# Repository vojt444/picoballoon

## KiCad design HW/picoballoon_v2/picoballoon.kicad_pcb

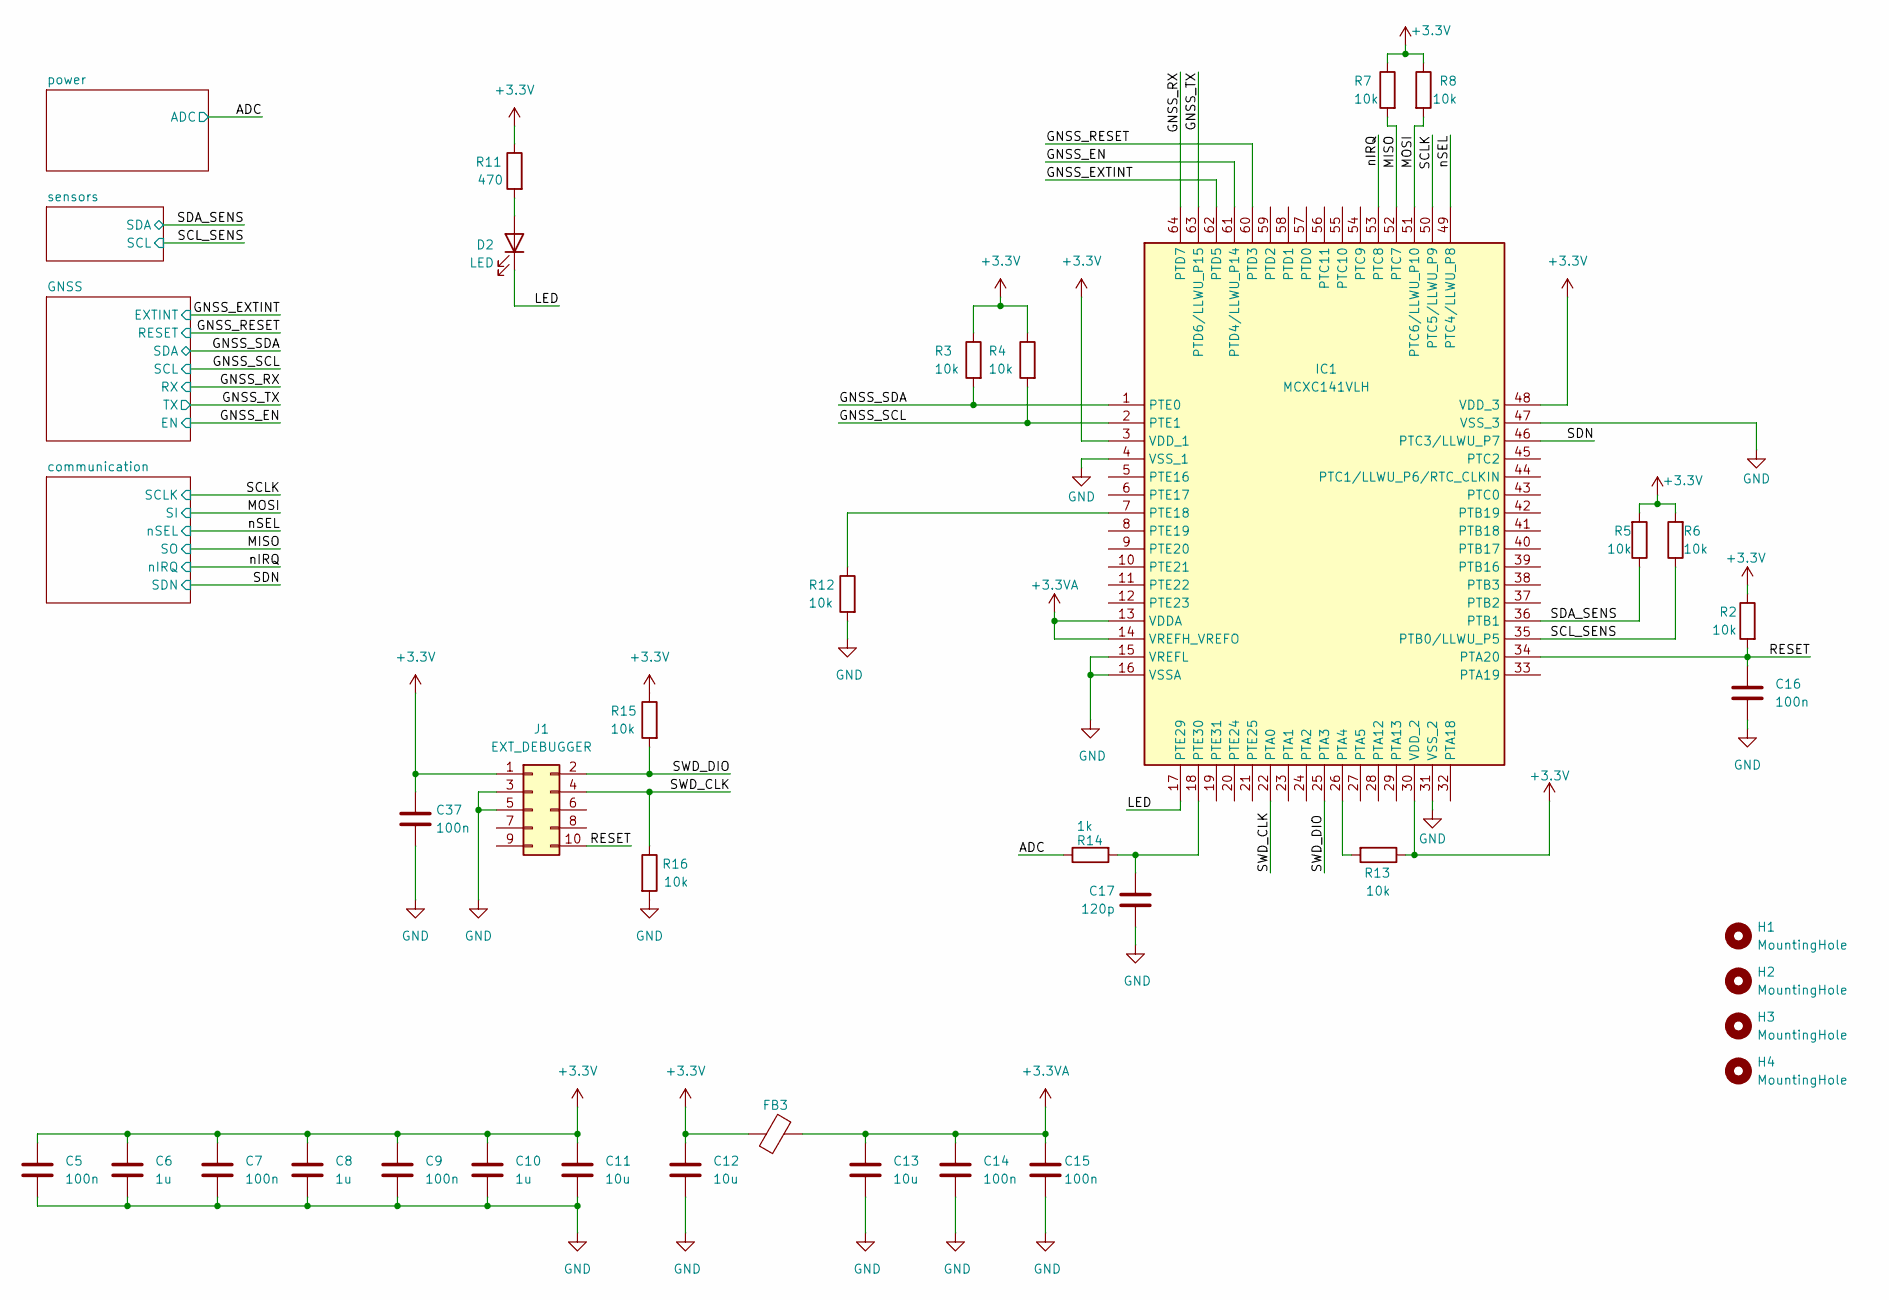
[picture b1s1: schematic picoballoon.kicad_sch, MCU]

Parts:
C5, C7, C9, C14, C15, C16, C37: 100n; C_0603_1608Metric_Pad1.08x0.95mm_HandSolder
C6, C8, C10: 1u; C_0603_1608Metric_Pad1.08x0.95mm_HandSolder
C11, C12, C13: 10u; C_0603_1608Metric_Pad1.08x0.95mm_HandSolder
C17: 120p; C_0603_1608Metric_Pad1.08x0.95mm_HandSolder
D2: LED; LED_0603_1608Metric_Pad1.05x0.95mm_HandSolder
FB3: FerriteBead; BLM21AG102BH1J
H1, H2, H3, H4: MountingHole; MountingHole_2.1mm
IC1: MCXC141VLH; LQFP-64-1EP_10x10mm_P0.5mm_EP5x5mm; Manufacturer_Part_Number MCXC141VLH; Mouser Part Number 771-MCXC141VLH
J1: EXT_DEBUGGER; PinHeader_2x05_P1.27mm_Vertical
R2, R3, R4, R5, R6, R7, R8, R12, R13, R15, R16: 10k; R_0603_1608Metric_Pad0.98x0.95mm_HandSolder
R11: 470; R_0603_1608Metric_Pad0.98x0.95mm_HandSolder
R14: 1k; R_0603_1608Metric_Pad0.98x0.95mm_HandSolder

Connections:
+3.3VA: C13.1, C14.1, C15.1, FB3.2, IC1.13 (VDDA), IC1.14 (VREFH_VREFO)
/ADC: R14.1; also elsewhere on the board
/GNSS_EN: IC1.61 (PTD4/LLWU_P14); also elsewhere on the board
/GNSS_EXTINT: IC1.62 (PTD5); also elsewhere on the board
/GNSS_RESET: IC1.60 (PTD3); also elsewhere on the board
/GNSS_RX: IC1.64 (PTD7); also elsewhere on the board
/GNSS_SCL: IC1.2 (PTE1), R4.2; also elsewhere on the board
/GNSS_SDA: IC1.1 (PTE0), R3.2; also elsewhere on the board
/GNSS_TX: IC1.63 (PTD6/LLWU_P15); also elsewhere on the board
/LED: D2.1 (K), IC1.17 (PTE29)
/MISO: IC1.52 (PTC7), R7.2; also elsewhere on the board
/MOSI: IC1.51 (PTC6/LLWU_P10), R8.2; also elsewhere on the board
/RESET: C16.1, IC1.34 (PTA20), J1.10, R2.2
/SCLK: IC1.50 (PTC5/LLWU_P9); also elsewhere on the board
/SCL_SENS: IC1.35 (PTB0/LLWU_P5), R6.1; also elsewhere on the board
/SDA_SENS: IC1.36 (PTB1), R5.1; also elsewhere on the board
/SDN: IC1.46 (PTC3/LLWU_P7); also elsewhere on the board
/SWD_CLK: IC1.22 (PTA0), J1.4, R16.1
/SWD_DIO: IC1.25 (PTA3), J1.2, R15.2
/nIRQ: IC1.53 (PTC8); also elsewhere on the board
/nSEL: IC1.49 (PTC4/LLWU_P8); also elsewhere on the board
unnamed: D2.2 (A), R11.2
unnamed: IC1.7 (PTE18), R12.1
unnamed: C17.1, IC1.18 (PTE30), R14.2

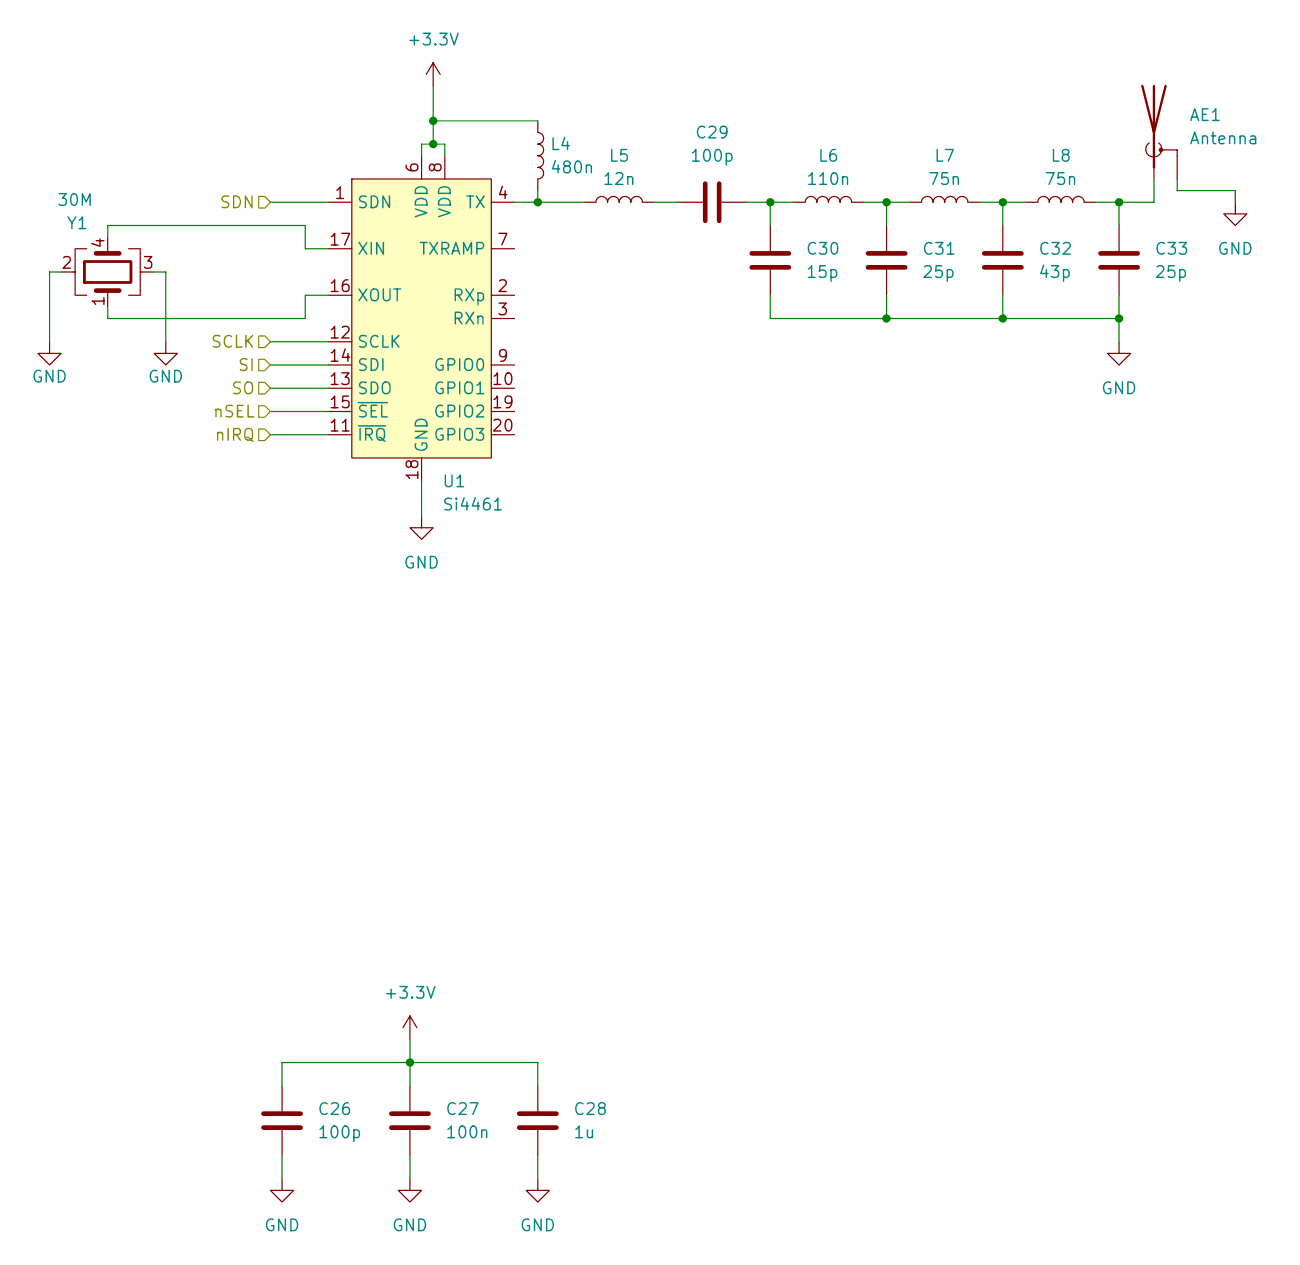
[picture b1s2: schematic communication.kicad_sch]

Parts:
AE1: Antenna; BNC_Connector_PCB
C26, C29: 100p; C_0603_1608Metric_Pad1.08x0.95mm_HandSolder
C27: 100n; C_0603_1608Metric_Pad1.08x0.95mm_HandSolder
C28: 1u; C_0603_1608Metric_Pad1.08x0.95mm_HandSolder
C30: 15p; C_0603_1608Metric_Pad1.08x0.95mm_HandSolder
C31, C33: 25p; C_0603_1608Metric_Pad1.08x0.95mm_HandSolder
C32: 43p; C_0603_1608Metric_Pad1.08x0.95mm_HandSolder
L4: 480n; L_0603_1608Metric_Pad1.05x0.95mm_HandSolder
L5: 12n; L_0603_1608Metric_Pad1.05x0.95mm_HandSolder
L6: 110n; L_0603_1608Metric_Pad1.05x0.95mm_HandSolder
L7, L8: 75n; L_0603_1608Metric_Pad1.05x0.95mm_HandSolder
U1: Si4461; QFN-20-1EP_4x4mm_P0.5mm_EP2.6x2.6mm_ThermalVias
Y1: 30M; ECS3002030BDUTR

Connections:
/MISO: U1.13 (SDO); also elsewhere on the board
/MOSI: U1.14 (SDI); also elsewhere on the board
/SCLK: U1.12 (SCLK); also elsewhere on the board
/SDN: U1.1 (SDN); also elsewhere on the board
/nIRQ: U1.11 (~IRQ); also elsewhere on the board
/nSEL: U1.15 (~SEL); also elsewhere on the board
unnamed: AE1.1 (A), C33.2, L8.2
unnamed: C29.1, L5.2
unnamed: C29.2, C30.2, L6.1
unnamed: C31.2, L6.2, L7.1
unnamed: C32.2, L7.2, L8.1
unnamed: L4.2, L5.1, U1.4 (TX)
unnamed: U1.17 (XIN), Y1.4
unnamed: U1.16 (XOUT), Y1.1

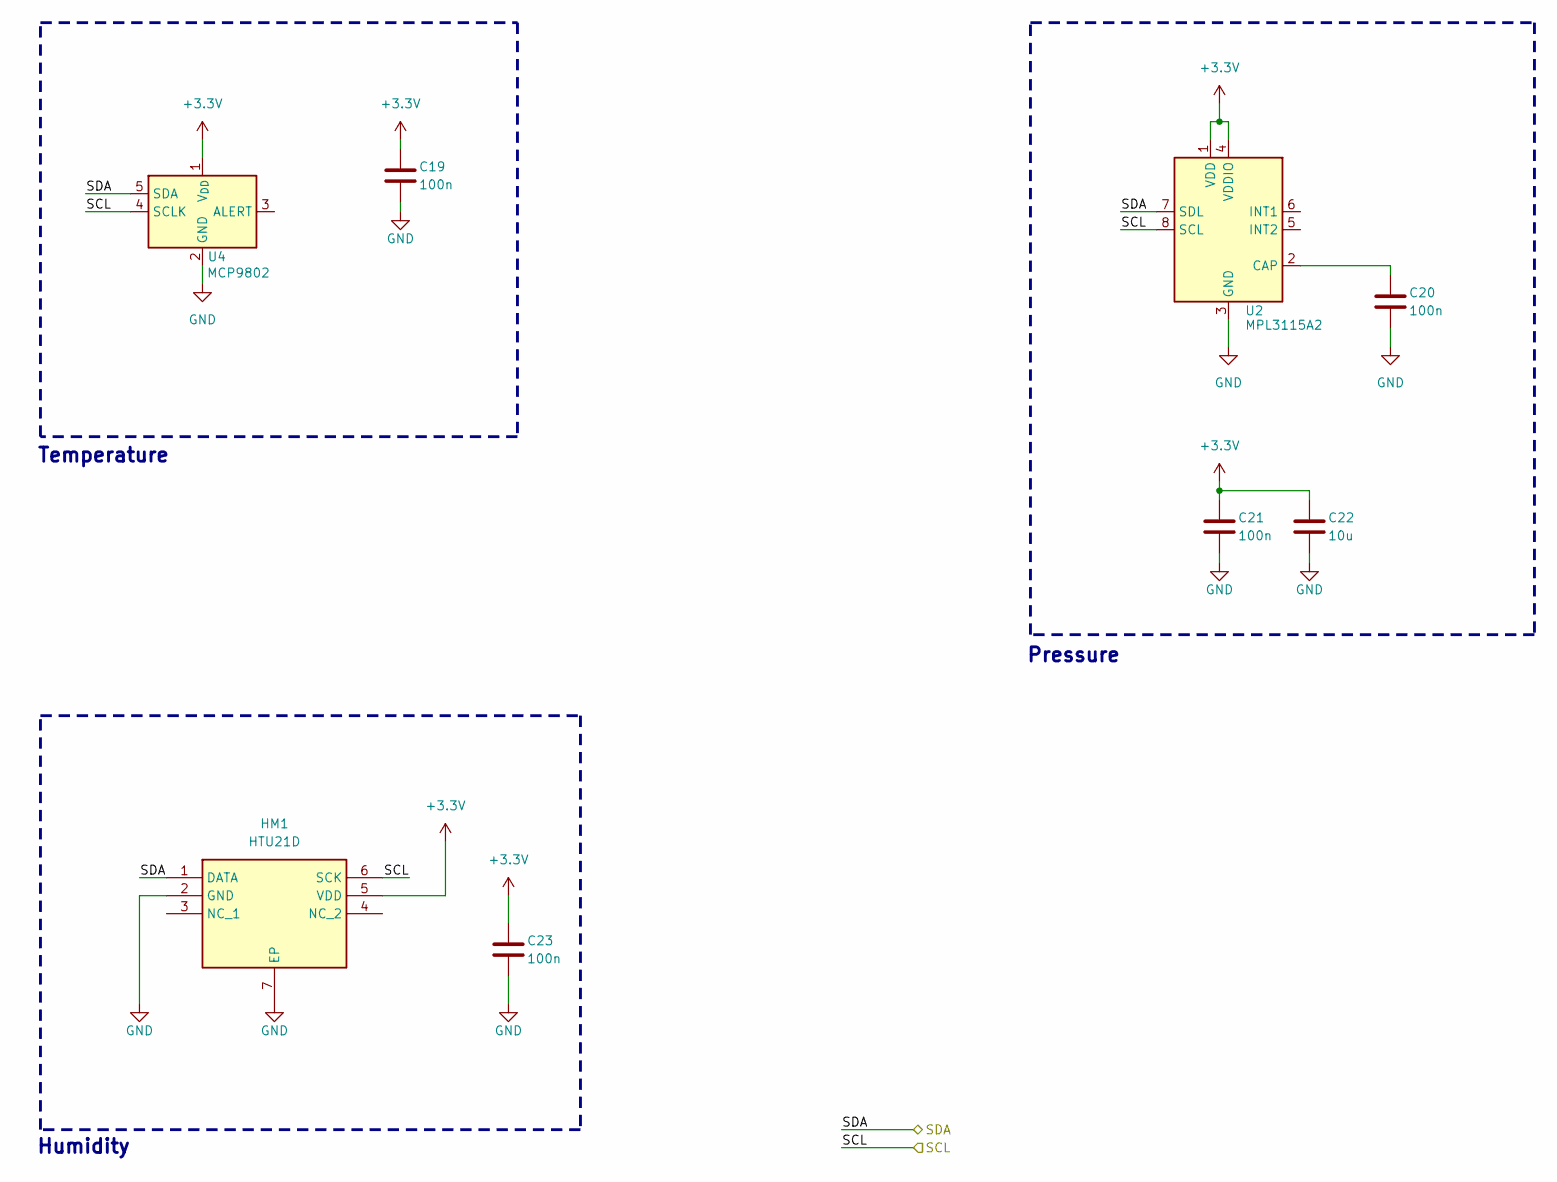
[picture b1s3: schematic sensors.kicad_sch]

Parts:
C19, C20, C21, C23: 100n; C_0603_1608Metric_Pad1.08x0.95mm_HandSolder
C22: 10u; C_0603_1608Metric_Pad1.08x0.95mm_HandSolder
HM1: HTU21D; SON100P300X300X100-7N-D; Mouser Part Number 824-HTU21D
U2: MPL3115A2; NXP_LGA-8_3x5mm_P1.25mm_H1.1mm
U4: MCP9802; SOT-23-5

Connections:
/SCL_SENS: HM1.6 (SCK), U2.8 (SCL), U4.4 (SCLK); also elsewhere on the board
/SDA_SENS: HM1.1 (DATA), U2.7 (SDL), U4.5 (SDA); also elsewhere on the board
unnamed: C20.1, U2.2 (CAP)

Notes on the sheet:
Pressure
Humidity
Temperature

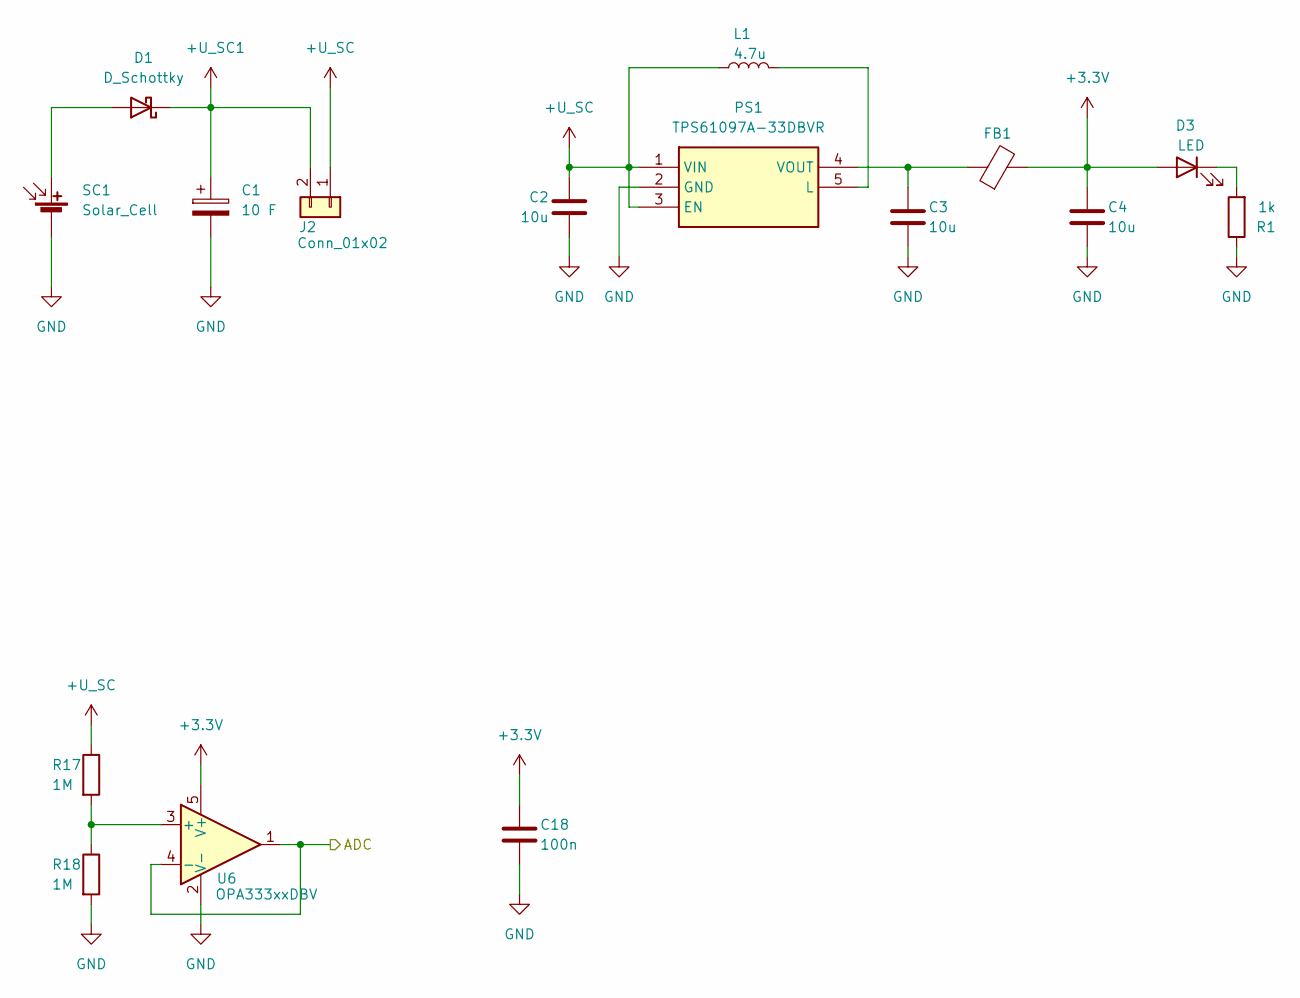
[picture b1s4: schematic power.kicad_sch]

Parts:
C1: 10 F; Supercap_7.5mm
C2, C3, C4: 10u; C_0603_1608Metric_Pad1.08x0.95mm_HandSolder
C18: 100n; C_0603_1608Metric_Pad1.08x0.95mm_HandSolder
D1: D_Schottky; Nexperia_CFP3_SOD-123W
D3: LED; LED_0603_1608Metric_Pad1.05x0.95mm_HandSolder
FB1: FerriteBead; BLM21AG102BH1J
J2: Conn_01x02; PinHeader_1x02_P2.54mm_Vertical
L1: 4.7u; L_0603_1608Metric_Pad1.05x0.95mm_HandSolder
PS1: TPS61097A-33DBVR; SOT95P280X145-5N; Mouser Part Number 595-TPS61097A-33DBVR
R1: 1k; R_0603_1608Metric_Pad0.98x0.95mm_HandSolder
R17, R18: 1M; R_0603_1608Metric_Pad0.98x0.95mm_HandSolder
SC1: Solar_Cell; PinHeader_1x02_P2.54mm_Vertical
U6: OPA333xxDBV; SOT-23-5

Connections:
+U_SC: C2.1, J2.1, L1.1, PS1.1 (VIN), PS1.3 (EN), R17.1
+U_SC1: C1.1, D1.1 (K), J2.2
/ADC: U6.1, U6.4 (-); also elsewhere on the board
unnamed: D1.2 (A), SC1.1 (+)
unnamed: D3.1 (K), R1.2
unnamed: L1.2, PS1.5 (L)
unnamed: C3.1, FB1.1, PS1.4 (VOUT)
unnamed: R17.2, R18.1, U6.3 (+)

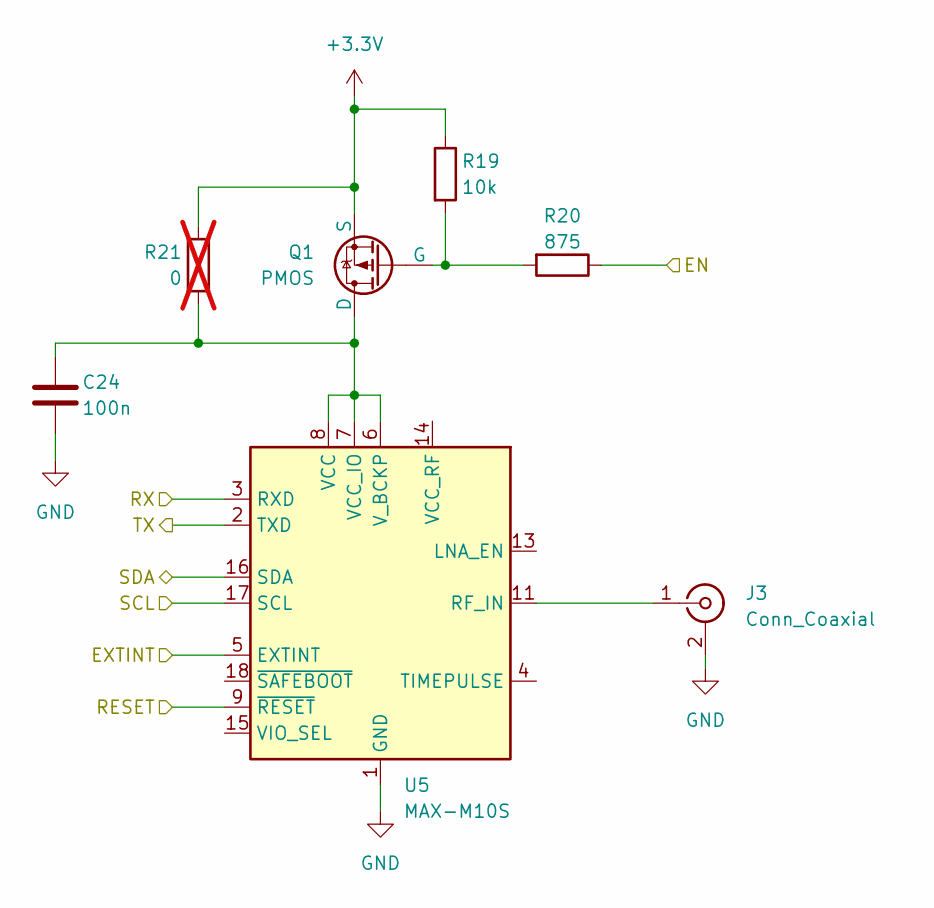
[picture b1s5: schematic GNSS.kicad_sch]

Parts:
C24: 100n; C_0603_1608Metric_Pad1.08x0.95mm_HandSolder
J3: Conn_Coaxial; U.FL_Molex_MCRF_73412-0110_Vertical
Q1: PMOS; SOT95P237X112-3N
R19: 10k; R_0603_1608Metric_Pad0.98x0.95mm_HandSolder
R20: 875; R_0603_1608Metric_Pad0.98x0.95mm_HandSolder
R21: 0; R_0603_1608Metric_Pad0.98x0.95mm_HandSolder; not fitted
U5: MAX-M10S; ublox_MAX

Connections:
/GNSS_EN: R20.1; also elsewhere on the board
/GNSS_EXTINT: U5.5 (EXTINT); also elsewhere on the board
/GNSS_RESET: U5.9 (~RESET); also elsewhere on the board
/GNSS_RX: U5.3 (RXD); also elsewhere on the board
/GNSS_SCL: U5.17 (SCL); also elsewhere on the board
/GNSS_SDA: U5.16 (SDA); also elsewhere on the board
/GNSS_TX: U5.2 (TXD); also elsewhere on the board
unnamed: J3.1 (In), U5.11 (RF_IN)
unnamed: C24.1, Q1.1 (D), R21.2, U5.6 (V_BCKP), U5.7 (VCC_IO), U5.8 (VCC)

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
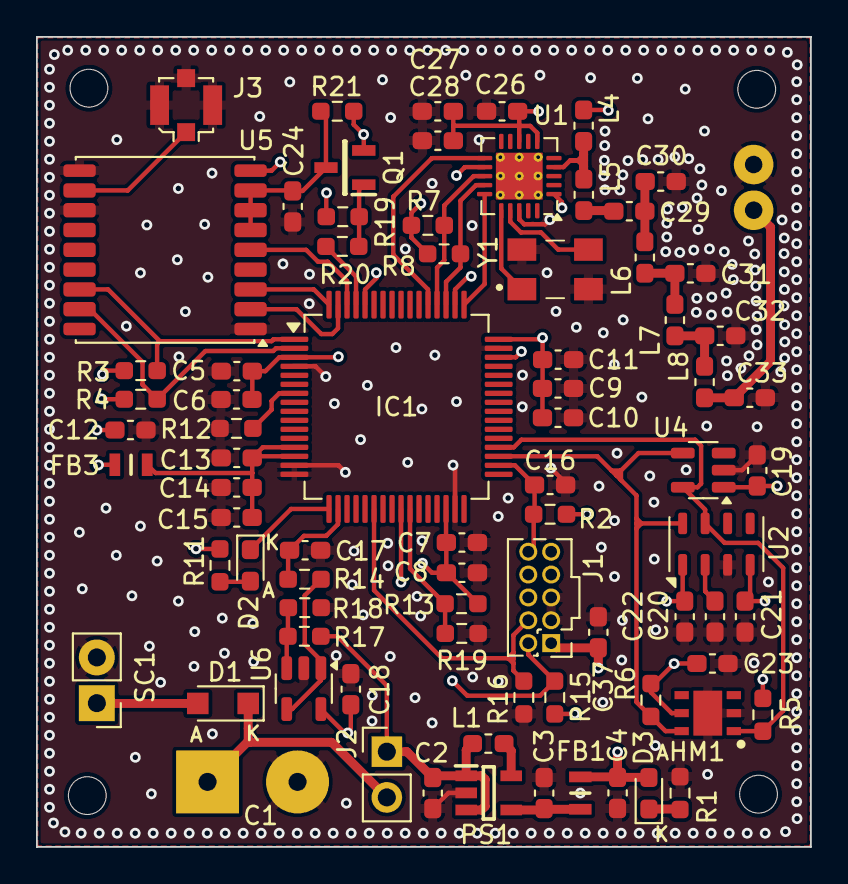
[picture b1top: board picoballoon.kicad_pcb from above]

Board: 4 copper layers, 43.0 x 45.0 mm, 83 parts (0 on the bottom side), 46 nets.

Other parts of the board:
R19#2: 10k; R_0603_1608Metric_Pad0.98x0.95mm_HandSolder

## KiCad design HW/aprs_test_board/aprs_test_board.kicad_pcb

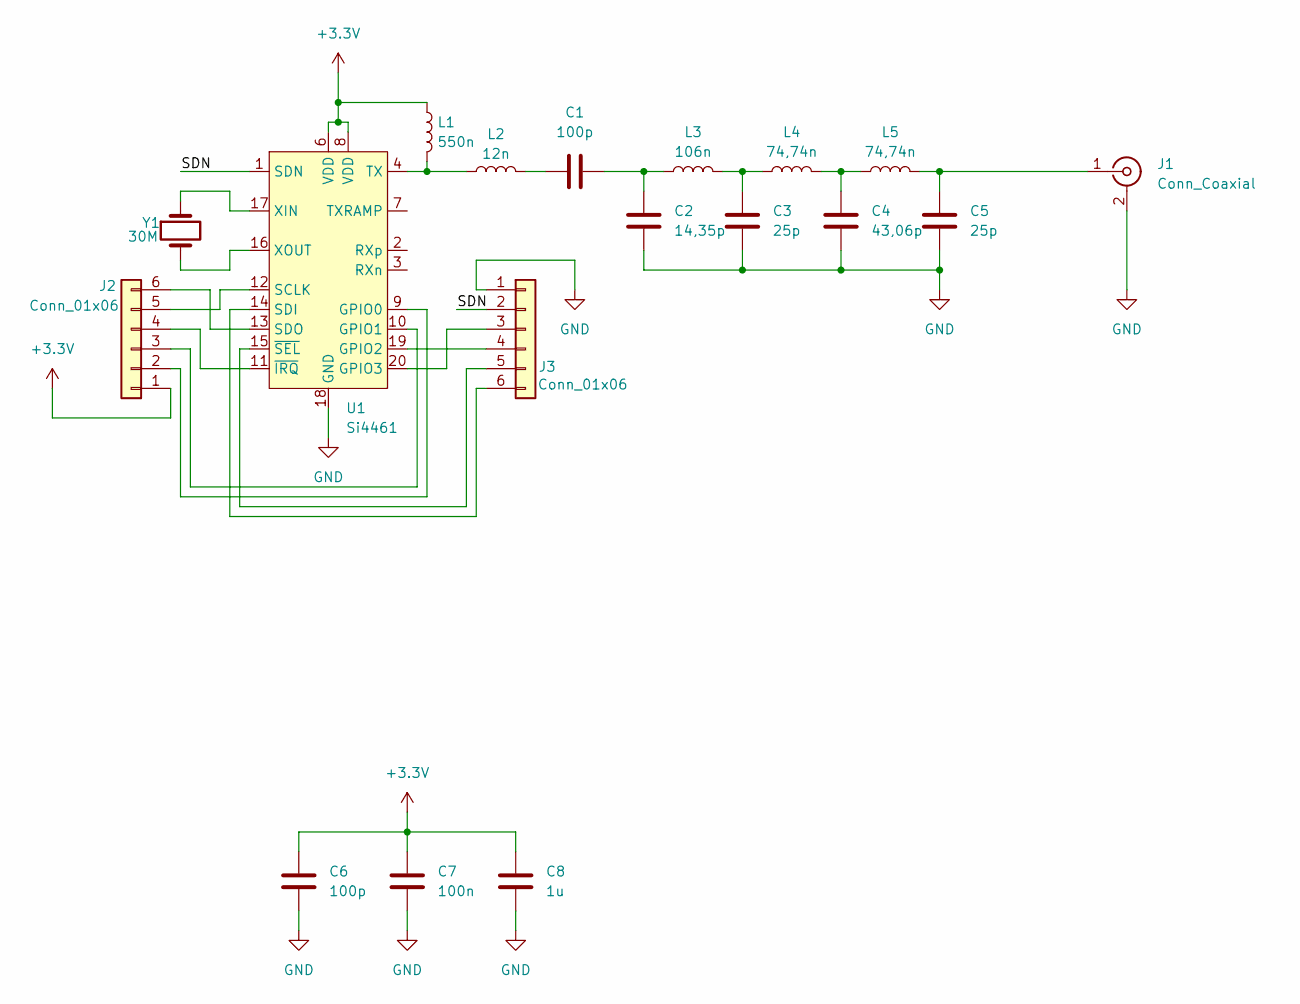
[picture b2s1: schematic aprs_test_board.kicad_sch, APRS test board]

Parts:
C1, C6: 100p; C_0805_2012Metric_Pad1.18x1.45mm_HandSolder
C2: 14,35p; C_0805_2012Metric_Pad1.18x1.45mm_HandSolder
C3, C5: 25p; C_0805_2012Metric_Pad1.18x1.45mm_HandSolder
C4: 43,06p; C_0805_2012Metric_Pad1.18x1.45mm_HandSolder
C7: 100n; C_0805_2012Metric_Pad1.18x1.45mm_HandSolder
C8: 1u; C_0805_2012Metric_Pad1.18x1.45mm_HandSolder
J1: Conn_Coaxial; BNC_Connector_PCB
J2, J3: Conn_01x06; PinHeader_1x06_P2.54mm_Vertical
L1: 550n; L_0805_2012Metric_Pad1.15x1.40mm_HandSolder
L2: 12n; L_0805_2012Metric_Pad1.15x1.40mm_HandSolder
L3: 106n; L_0805_2012Metric_Pad1.15x1.40mm_HandSolder
L4, L5: 74,74n; L_0805_2012Metric_Pad1.15x1.40mm_HandSolder
U1: Si4461; QFN-20-1EP_4x4mm_P0.5mm_EP2.6x2.6mm_ThermalVias
Y1: 30M; ECS3002030BDUTR

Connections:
+3.3V: C6.1, C7.1, C8.1, J2.1, L1.1, U1.6 (VDD), U1.8 (VDD)
/SDN: J3.2, U1.1 (SDN)
GND: C2.1, C3.1, C4.1, C5.1, C6.2, C7.2, C8.2, J1.2 (Ext), J3.1, U1.18 (GND), U1.21 (GND), Y1.3, Y1.4
unnamed: C1.1, L2.2
unnamed: C1.2, C2.2, L3.1
unnamed: C3.2, L3.2, L4.1
unnamed: C4.2, L4.2, L5.1
unnamed: C5.2, J1.1 (In), L5.2
unnamed: J2.2, U1.9 (GPIO0)
unnamed: J2.3, U1.10 (GPIO1)
unnamed: J2.4, U1.11 (~IRQ)
unnamed: J2.5, U1.12 (SCLK)
unnamed: J2.6, U1.13 (SDO)
unnamed: J3.3, U1.20 (GPIO3)
unnamed: J3.4, U1.19 (GPIO2)
unnamed: J3.5, U1.15 (~SEL)
unnamed: J3.6, U1.14 (SDI)
unnamed: L1.2, L2.1, U1.4 (TX)
unnamed: U1.17 (XIN), Y1.1
unnamed: U1.16 (XOUT), Y1.2

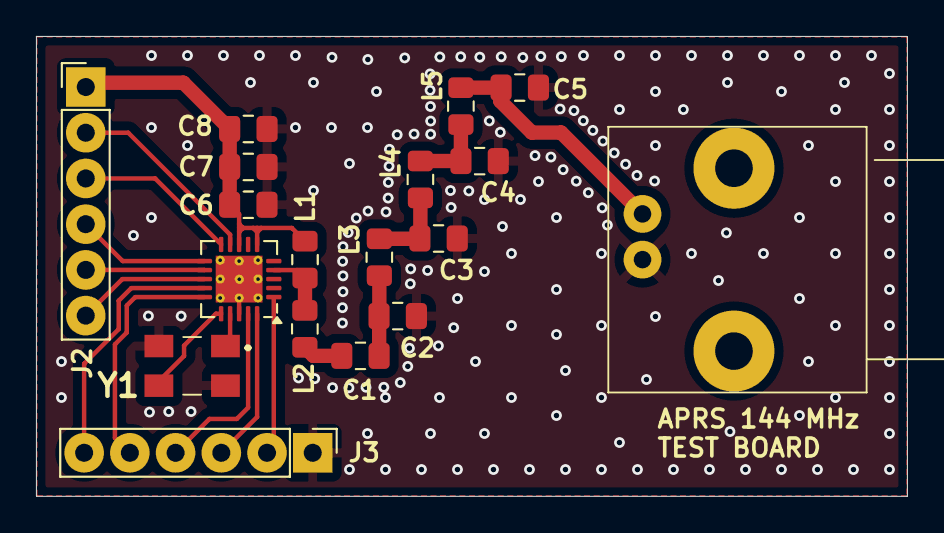
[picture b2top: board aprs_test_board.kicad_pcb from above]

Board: 2 copper layers, 48.4 x 25.5 mm, 18 parts (0 on the bottom side), 20 nets.

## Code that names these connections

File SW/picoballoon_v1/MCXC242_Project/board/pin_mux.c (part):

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pin_labels:
- {pin_num: '1', pin_signal: PTE0/CLKOUT32K/SPI1_MISO/LPUART1_TX/RTC_CLKOUT/CMP0_OUT/I2C1_SDA, label: 'J3[1]/UART1_TX', identifier: SDA_GNSS}
- {pin_num: '54', pin_signal: CMP0_IN3/PTC9/I2C0_SDA/TPM0_CH5, label: D6-TPM0_CH5/CMP0_IN3, identifier: BELL202}
- {pin_num: '53', pin_signal: CMP0_IN2/PTC8/I2C0_SCL/TPM0_CH4, label: D7-TPM0_CH4/CMP0_IN2, identifier: nIRQ}
- {pin_num: '49', pin_signal: PTC4/LLWU_P8/SPI0_PCS0/LPUART1_TX/TPM0_CH3/SPI1_PCS0, label: D10-SPI0_CS0, identifier: CS}
- {pin_num: '51', pin_signal: CMP0_IN0/PTC6/LLWU_P10/SPI0_MOSI/EXTRG_IN/SPI0_MISO, label: D11-SPI0_MOSI, identifier: MOSI}
- {pin_num: '52', pin_signal: CMP0_IN1/PTC7/SPI0_MISO/USB_SOF_OUT/SPI0_MOSI, label: D12-SPI0_MISO, identifier: MISO}
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- {pin_num: '63', pin_signal: ADC0_SE7b/PTD6/LLWU_P15/SPI1_MOSI/LPUART0_RX/I2C1_SDA/SPI1_MISO/FXIO0_D6, label: D14-I2C1_SDA/ACCELL_SDA, identifier: RX}
- {pin_num: '64', pin_signal: PTD7/SPI1_MISO/LPUART0_TX/I2C1_SCL/SPI1_MOSI/FXIO0_D7, label: D15-I2C1_SCL/ACCELL_SCL, identifier: TX}
- {pin_num: '9', pin_signal: ADC0_DP0/ADC0_SE0/PTE20/TPM1_CH0/LPUART0_TX/FXIO0_D4, label: A2-ADC0_SE0, identifier: voltage;VOLTAGE}
- {pin_num: '36', pin_signal: ADC0_SE9/PTB1/I2C0_SDA/TPM1_CH1/SPI1_MISO/SPI1_MOSI, label: A4-I2C0_SDA/ADC0_SE9, identifier: SDA_SENS}
- {pin_num: '35', pin_signal: ADC0_SE8/PTB0/LLWU_P5/I2C0_SCL/TPM1_CH0/SPI1_MOSI/SPI1_MISO, label: A5-I2C0_SCL/ADC0_SE8, identifier: SC_SENS;SCL_SENS}
- {pin_num: '2', pin_signal: PTE1/SPI1_MOSI/LPUART1_RX/SPI1_MISO/I2C1_SCL, label: 'J3[3]/UART1_RX', identifier: SCL_GNSS}
- {pin_num: '61', pin_signal: PTD4/LLWU_P14/SPI1_PCS0/UART2_RX/TPM0_CH4/FXIO0_D4, label: 'J1[9]', identifier: GNSS_EN}
- {pin_num: '62', pin_signal: ADC0_SE6b/PTD5/SPI1_SCK/UART2_TX/TPM0_CH5/FXIO0_D5, label: 'J1[11]/J3[2]/SDA_PTD5', identifier: EXTINT_GNSS}
- {pin_num: '55', pin_signal: PTC10/I2C1_SCL, label: 'J2[1]', identifier: BELL202}
- {pin_num: '46', pin_signal: PTC3/LLWU_P7/SPI1_SCK/LPUART1_RX/TPM0_CH2/CLKOUT, label: 'J2[15]', identifier: SDN}
- {pin_num: '38', pin_signal: ADC0_SE13/PTB3/I2C0_SDA/TPM2_CH1, label: 'J1[13]', identifier: SDA_TEMP}
- {pin_num: '37', pin_signal: ADC0_SE12/PTB2/I2C0_SCL/TPM2_CH0, label: 'J1[15]', identifier: SCL_TEMP}
- {pin_num: '17', pin_signal: CMP0_IN5/ADC0_SE4b/PTE29/TPM0_CH2/TPM_CLKIN0, label: LED, identifier: LED}
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- options: {createDeInit: 'true', callFromInitBoot: 'true', coreID: core0, enableClock: 'true'}
- pin_list:
  - {pin_num: '9', peripheral: ADC0, signal: 'SE, 0', pin_signal: ADC0_DP0/ADC0_SE0/PTE20/TPM1_CH0/LPUART0_TX/FXIO0_D4, identifier: VOLTAGE}
  - {pin_num: '35', peripheral: I2C0, signal: SCL, pin_signal: ADC0_SE8/PTB0/LLWU_P5/I2C0_SCL/TPM1_CH0/SPI1_MOSI/SPI1_MISO, identifier: SCL_SENS}
  - {pin_num: '36', peripheral: I2C0, signal: SDA, pin_signal: ADC0_SE9/PTB1/I2C0_SDA/TPM1_CH1/SPI1_MISO/SPI1_MOSI}
  - {pin_num: '46', peripheral: GPIOC, signal: 'GPIO, 3', pin_signal: PTC3/LLWU_P7/SPI1_SCK/LPUART1_RX/TPM0_CH2/CLKOUT, direction: OUTPUT}
  - {pin_num: '49', peripheral: GPIOC, signal: 'GPIO, 4', pin_signal: PTC4/LLWU_P8/SPI0_PCS0/LPUART1_TX/TPM0_CH3/SPI1_PCS0, direction: OUTPUT, gpio_init_state: 'true'}
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  - {pin_num: '19', peripheral: n/a, signal: disabled, pin_signal: PTE31/TPM0_CH4}
  - {pin_num: '20', peripheral: n/a, signal: disabled, pin_signal: PTE24/TPM0_CH0/I2C0_SCL}
  - {pin_num: '21', peripheral: n/a, signal: disabled, pin_signal: PTE25/TPM0_CH1/I2C0_SDA}
  - {pin_num: '22', peripheral: n/a, signal: disabled, pin_signal: PTA0/TPM0_CH5/SWD_CLK, pull_enable: disable}
  - {pin_num: '23', peripheral: n/a, signal: disabled, pin_signal: PTA1/LPUART0_RX/TPM2_CH0}
  - {pin_num: '24', peripheral: n/a, signal: disabled, pin_signal: PTA2/LPUART0_TX/TPM2_CH1}
  - {pin_num: '25', peripheral: n/a, signal: disabled, pin_signal: PTA3/I2C1_SCL/TPM0_CH0/SWD_DIO, pull_enable: disable}
  - {pin_num: '26', peripheral: n/a, signal: disabled, pin_signal: PTA4/I2C1_SDA/TPM0_CH1/NMI_b, pull_enable: disable, passive_filter: disable}
  - {pin_num: '27', peripheral: n/a, signal: disabled, pin_signal: PTA5/USB_CLKIN/TPM0_CH2}
  - {pin_num: '28', peripheral: n/a, signal: disabled, pin_signal: PTA12/TPM1_CH0}
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                                                .passiveFilterEnable = kPORT_PassiveFilterDisable,
                                                /* Low drive strength is configured */
                                                .driveStrength = kPORT_LowDriveStrength,
                                                /* Pin is configured as SWD_CLK */
                                                .mux = kPORT_MuxAlt7};
    /* PORTA0 (pin 22) is configured as SWD_CLK */
    PORT_SetPinConfig(BOARD_INIT_SLEEP_PINS_DEINIT_DEBUG_SWD_SWDCLK_PORT, BOARD_INIT_SLEEP_PINS_DEINIT_DEBUG_SWD_SWDCLK_PIN, &DEBUG_SWD_SWDCLK);

    /* PORTA1 (pin 23) is disabled */
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                                               .passiveFilterEnable = kPORT_PassiveFilterDisable,
                                               /* Low drive strength is configured */
                                               .driveStrength = kPORT_LowDriveStrength,
                                               /* Pin is configured as SWD_DIO */
                                               .mux = kPORT_MuxAlt7};
    /* PORTA3 (pin 25) is configured as SWD_DIO */
    PORT_SetPinConfig(BOARD_INIT_SLEEP_PINS_DEINIT_DEBUG_SWD_SWDIO_PORT, BOARD_INIT_SLEEP_PINS_DEINIT_DEBUG_SWD_SWDIO_PIN, &DEBUG_SWD_SWDIO);

    const port_pin_config_t SW3 = {/* Internal pull-up resistor is enabled */
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
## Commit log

2024-10-15 kicad project
2024-10-15 impedance matching
2024-10-17 aprs test board
2024-10-19 APRS test board done
2024-10-20 test board
2024-10-23 gerber files
2024-10-23 little fix
2024-10-23 sharp angles fix
2024-10-30 some devices replaced
2024-11-11 aprs test board fixed
2024-12-13 picoballoon pcb
2024-12-13 minor fixes
2024-12-14 test points
2024-12-27 mcxc
2024-12-28 gnss antenna
2024-12-28 mounting holes
2024-12-28 old PCB rename
2024-12-28 pdf removed
2024-12-28 power supply change
2024-12-28 little changes
2024-12-29 test board 3D
2025-02-13 APRS testing with Arduinno
2025-02-17 test FW, not working yet
2025-03-03 gerbers
2025-03-23 gitignore for C project
2025-03-23 FW for temp sensor and ADC
2025-03-24 c file moved to the correct folder
2025-03-28 SPI is working :)
2025-03-30 communication with si4461 is now working
2025-04-02 get info is working
2025-04-10 working on FW
2025-04-10 PCB v2 starting
2025-04-10 little changes in scheme
2025-04-12 PCB v2
2025-04-12 minor changes
2025-04-12 GND fix
2025-05-12 picoballoon code
2025-05-13 little improvements
2025-05-17 pokusy
2025-05-20 final
